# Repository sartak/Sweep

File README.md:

# sartak's fork of Ferris Sweep

|                     Front                     |                    Back                     |
| :-------------------------------------------: | :-----------------------------------------: |
|  |  |

This is a fork of [Sweep](https://github.com/davidphilipbarr/Sweep) with the following modifications to the Half-Swept board:

- Removed all the silkscreen text and markings (so you better already know how to build one of these!)
- Refined the top edge to be staggered with the keys, a la [Ben Vallack](https://www.youtube.com/watch?v=JqpBKuEVinw)
- Adjusted the position of the power switch and reset button
- Removed tenting puck and holes unnecessary for Kailh choc v1 switches

The [`half-swept_gerber.zip`](https://github.com/sartak/Sweep/raw/main/Sweep%20half-swept/half-swept_gerber.zip) has been updated, ready to be sent to a PCB manufacturer.

My impressions so far:

- Tidying up the PCB feels real nice! When I'm using the keyboard, I appreciate that there are no distractions—no tenting holes peeking through keycaps, no overhang above the top row… I can't even see the power switch or reset button unless I'm above looking nearly straight down. And of course, no noisy silkscreen or superfluous holes makes the board feel more premium when inspecting the reverse sides.
- (Changed) The reset button is a hair too close to the switch below it. It works, but only _just_ barely. There's a ~1 millimeter gap. Next revision will fix that.
- I've only done a wired build so far, but I'm satisfied with the multimeter testing I did for the power switch and battery, so I'm sure wireless will work.

See [https://github.com/sartak/keyboard](https://github.com/sartak/keyboard) for how I use this.

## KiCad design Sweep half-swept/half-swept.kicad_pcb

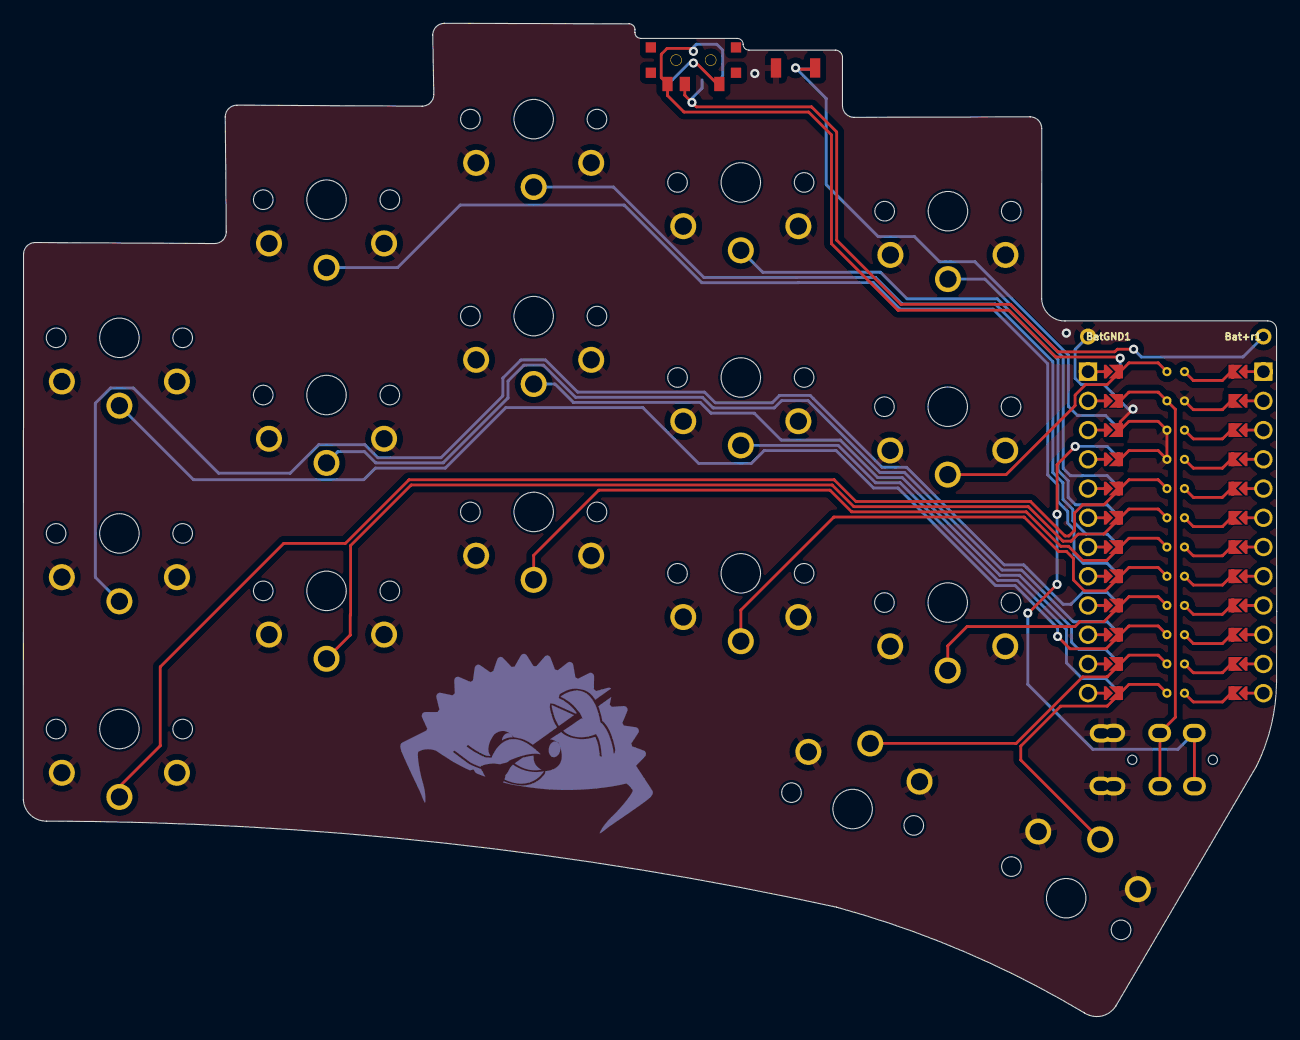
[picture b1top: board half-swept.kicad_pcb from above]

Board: 2 copper layers, 108.9 x 86.3 mm, 24 parts (0 on the bottom side), 23 nets.

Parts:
 : Tenting_Puck2
 #2: SW_SPDT; SPDT_C128955
Bat+r1: MountingHole_Pad; 1pin_conn
BatGND1: MountingHole_Pad; 1pin_conn
J2: AudioJack4dpb; TRRS-PJ-DPB2
RSW2: SW_Push; Tactile-Switch_SMT
SW1, SW2, SW3, SW4, SW5, SW6, SW7, SW8, SW9, SW10, SW11, SW12, SW13, SW14, SW15, SW16, SW17: SW_Push; SW_PG1350_rev_DPB
U1: ProMicro-kbd; ProMicro_jumpers_facedown

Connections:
BT+_r: #2.2, Bat+r1.1
Switch1: SW1.1, U1.10
Switch2: SW2.1, U1.17
Switch3: SW3.1, U1.18
Switch4: SW4.1, U1.19
Switch5: SW5.1, U1.20
Switch6: SW6.1, U1.16
Switch7: SW7.1, U1.15
Switch8: SW8.1, U1.14
Switch9: SW9.1, U1.13
Switch10: SW10.1, U1.1
Switch11: SW11.1, U1.5
Switch12: SW12.1, U1.6
Switch13: SW13.1, U1.7
Switch14: SW14.1, U1.8
Switch15: SW15.1, U1.9
Switch16: SW16.1, U1.11
Switch17: SW17.1, U1.12
Switch18: J2.R1, U1.2
gnd: BatGND1.1, J2.S, J2.T, RSW2.1, RSW2.2, SW1.2, SW2.2, SW3.2, SW4.2, SW5.2, SW6.2, SW7.2, SW8.2, SW9.2, SW10.2, SW11.2, SW12.2, SW13.2, SW14.2, SW15.2, SW16.2, SW17.2, U1.3, U1.4, U1.23
raw: #2.3, U1.24
reset: RSW2.1, RSW2.2, U1.22
vcc: J2.R2, U1.21

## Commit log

2022-12-04 Remove tenting puck
2022-12-04 Remove TRRS alignment lines
2022-12-04 Remove MCU alignment lines
2022-12-04 Remove alignment corners for switches
2022-12-04 Remove text from silkscreen
2022-12-04 Remove battery alignment lines
2022-12-04 Remove reset alignment lines
2022-12-04 Move the reset and power switches
2022-12-04 Remove unnecessary through-holes from switches
2022-12-04 Pull in the edge cut
2022-12-04 Tweak reset trace
2022-12-04 Regenerate gerber
2022-12-04 Remove other boards and files
2022-12-04 Rewrite README with new screenshots
2022-12-04 Tweaks to satisfy the Design Rules Checker
2022-12-07 Better title
2022-12-07 Add link to keyboard repo
2022-12-20 Now that I've gotten and built one, some initial impressions
2022-12-20 Manufactured photo
2022-12-20 Tweaked readme
2023-02-11 add measurements
2025-01-25 Added more separation between the reset button and the switch below
2025-01-25 Gerber files generated
